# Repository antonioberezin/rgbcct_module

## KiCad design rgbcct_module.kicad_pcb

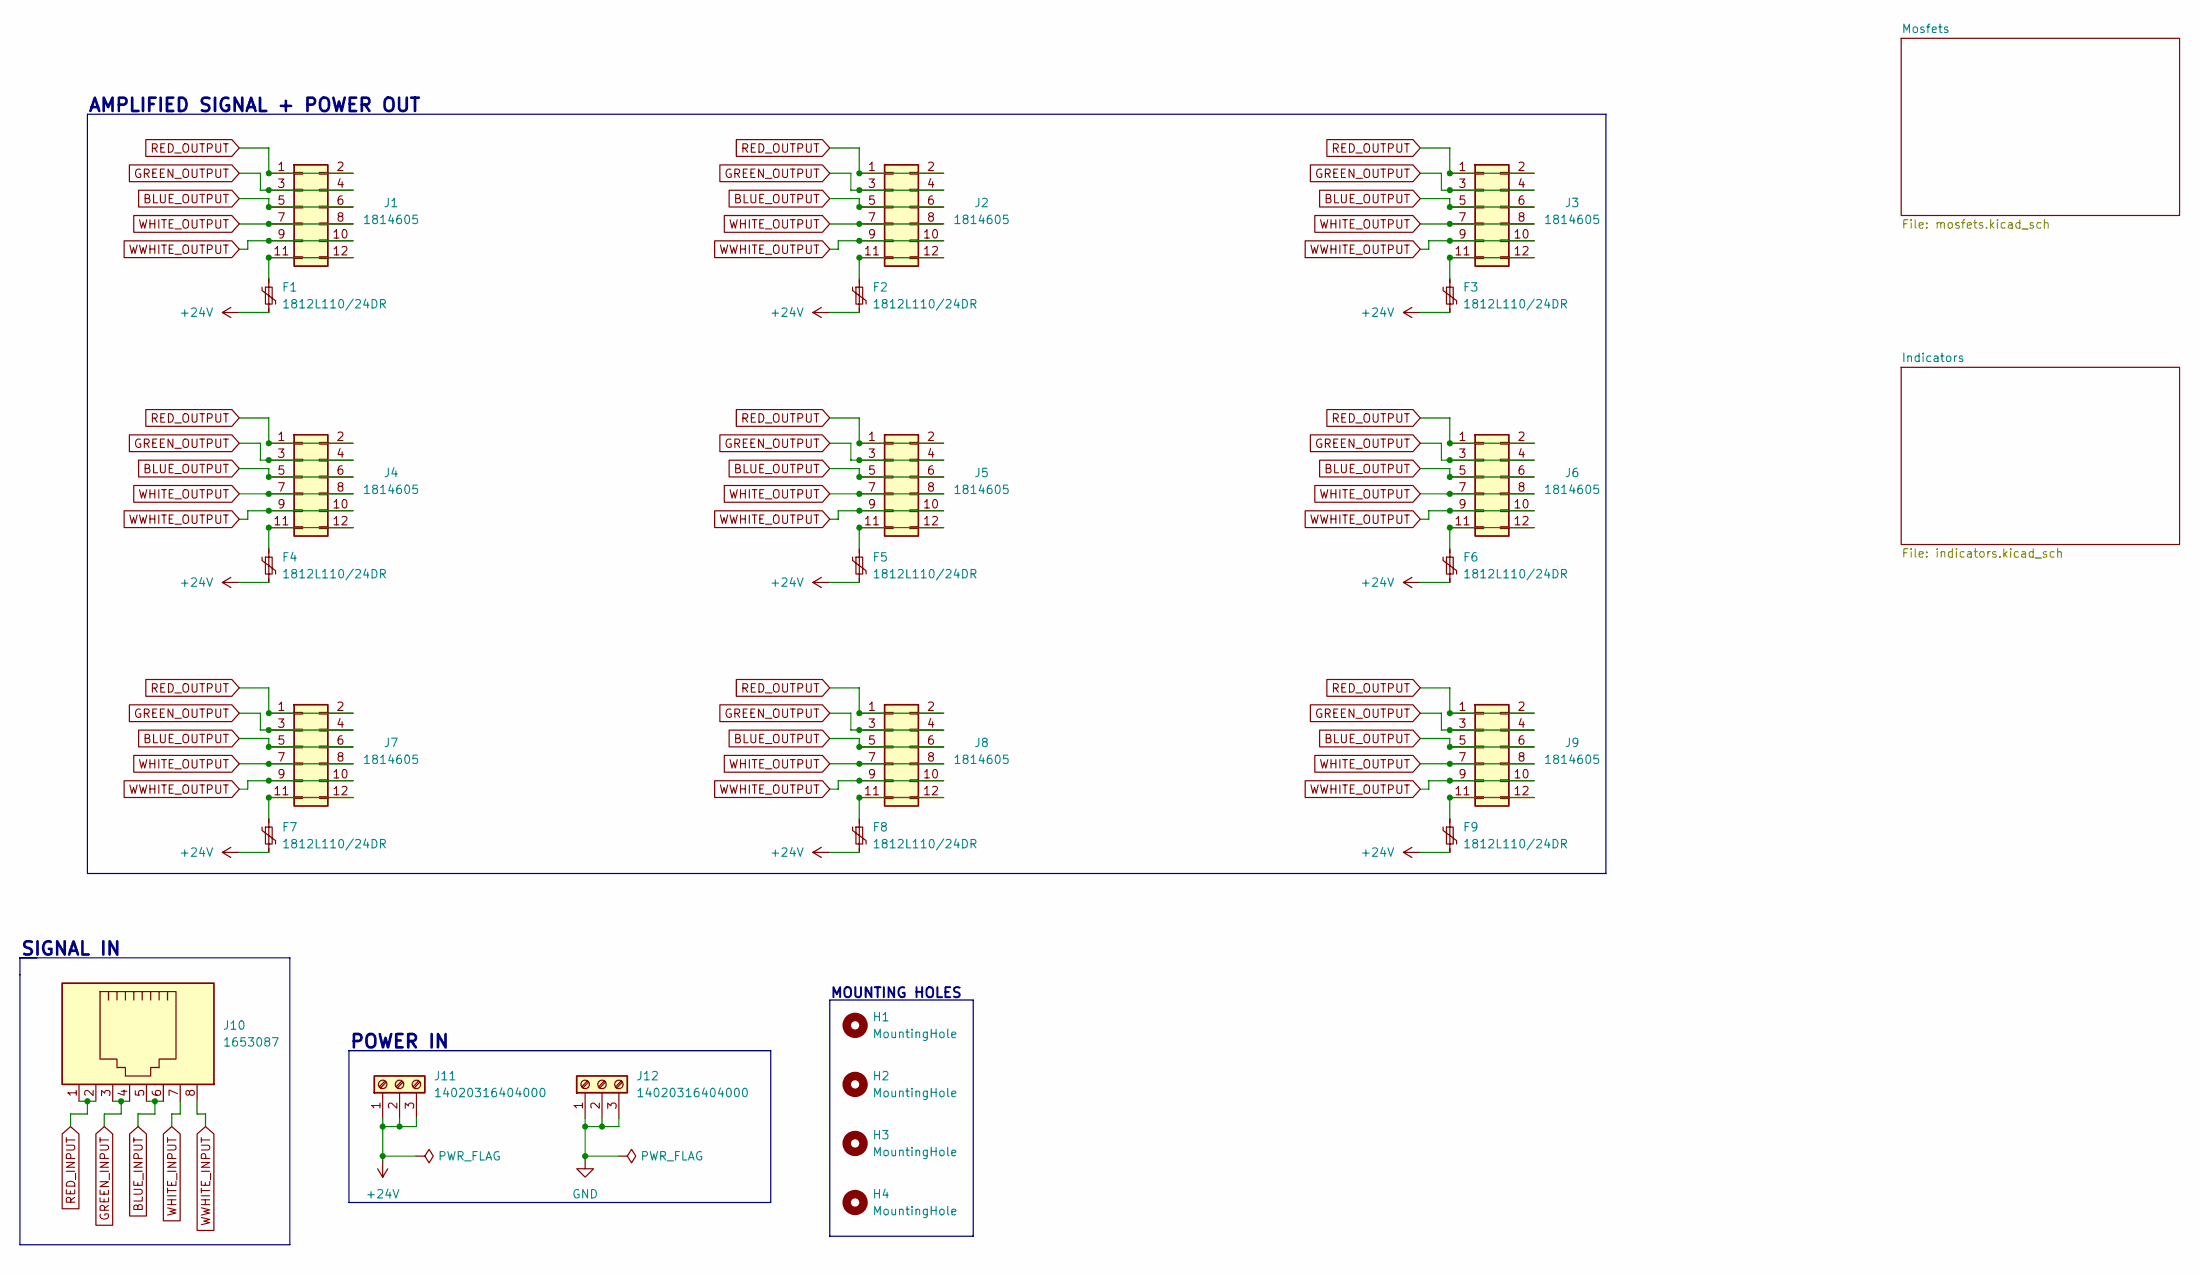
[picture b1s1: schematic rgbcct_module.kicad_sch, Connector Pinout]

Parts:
F1, F2, F3, F4, F5, F6, F7, F8, F9: 1812L110/24DR; 1812L110
H1, H2, H3, H4: MountingHole; MountingHole_3.2mm_M3
J1, J2, J3, J4, J5, J6, J7, J8, J9: 1814605
J10: 1653087
J11, J12: 14020316404000

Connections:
+24V: F1.2, F2.2, F3.2, F4.2, F5.2, F6.2, F7.2, F8.2, F9.2, J11.1, J11.2, J11.3; also elsewhere on the board
BLUE_INPUT: J10.5, J10.6; also elsewhere on the board
BLUE_OUTPUT: J1.5, J1.6, J2.5, J2.6, J3.5, J3.6, J4.5, J4.6, J5.5, J5.6, J6.5, J6.6, J7.5, J7.6, J8.5, J8.6, J9.5, J9.6; also elsewhere on the board
GND: J10.9, J10.10, J10.11, J10.12, J12.1, J12.2, J12.3; also elsewhere on the board
GREEN_INPUT: J10.3, J10.4; also elsewhere on the board
GREEN_OUTPUT: J1.3, J1.4, J2.3, J2.4, J3.3, J3.4, J4.3, J4.4, J5.3, J5.4, J6.3, J6.4, J7.3, J7.4, J8.3, J8.4, J9.3, J9.4; also elsewhere on the board
unnamed: F1.1, J1.11, J1.12
unnamed: F2.1, J2.11, J2.12
unnamed: F3.1, J3.11, J3.12
unnamed: F4.1, J4.11, J4.12
unnamed: F5.1, J5.11, J5.12
unnamed: F6.1, J6.11, J6.12
unnamed: F7.1, J7.11, J7.12
unnamed: F8.1, J8.11, J8.12
unnamed: F9.1, J9.11, J9.12
RED_INPUT: J10.1, J10.2; also elsewhere on the board
RED_OUTPUT: J1.1, J1.2, J2.1, J2.2, J3.1, J3.2, J4.1, J4.2, J5.1, J5.2, J6.1, J6.2, J7.1, J7.2, J8.1, J8.2, J9.1, J9.2; also elsewhere on the board
WHITE_INPUT: J10.7; also elsewhere on the board
WHITE_OUTPUT: J1.7, J1.8, J2.7, J2.8, J3.7, J3.8, J4.7, J4.8, J5.7, J5.8, J6.7, J6.8, J7.7, J7.8, J8.7, J8.8, J9.7, J9.8; also elsewhere on the board
WWHITE_INPUT: J10.8; also elsewhere on the board
WWHITE_OUTPUT: J1.9, J1.10, J2.9, J2.10, J3.9, J3.10, J4.9, J4.10, J5.9, J5.10, J6.9, J6.10, J7.9, J7.10, J8.9, J8.10, J9.9, J9.10; also elsewhere on the board

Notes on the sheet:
MOUNTING HOLES
SIGNAL IN
AMPLIFIED SIGNAL + POWER OUT
POWER IN

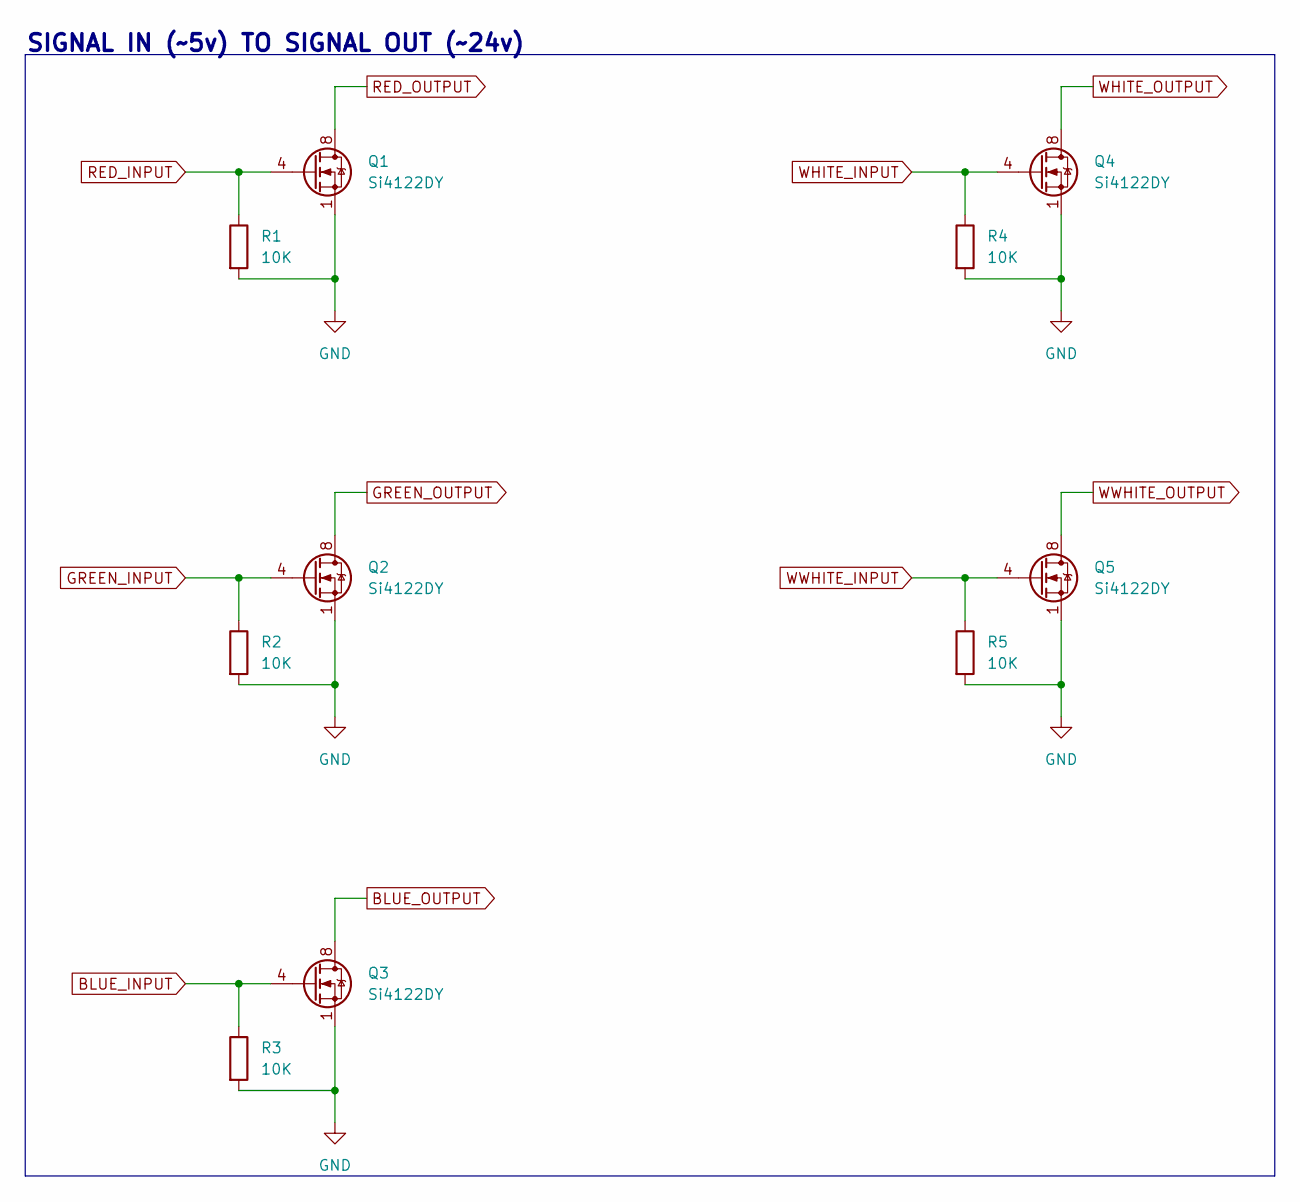
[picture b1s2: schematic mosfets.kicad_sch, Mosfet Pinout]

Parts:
Q1, Q2, Q3, Q4, Q5: Si4122DY
R1, R2, R3, R4, R5: 10K; Panasonic_ERJ_0805

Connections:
BLUE_INPUT: Q3.4 (G), R3.1; also elsewhere on the board
BLUE_OUTPUT: Q3.5 (D), Q3.6 (D), Q3.7 (D), Q3.8 (D); also elsewhere on the board
GND: Q1.1 (S), Q1.2 (S), Q1.3 (S), Q2.1 (S), Q2.2 (S), Q2.3 (S), Q3.1 (S), Q3.2 (S), Q3.3 (S), Q4.1 (S), Q4.2 (S), Q4.3 (S), Q5.1 (S), Q5.2 (S), Q5.3 (S), R1.2, R2.2, R3.2, R4.2, R5.2; also elsewhere on the board
GREEN_INPUT: Q2.4 (G), R2.1; also elsewhere on the board
GREEN_OUTPUT: Q2.5 (D), Q2.6 (D), Q2.7 (D), Q2.8 (D); also elsewhere on the board
RED_INPUT: Q1.4 (G), R1.1; also elsewhere on the board
RED_OUTPUT: Q1.5 (D), Q1.6 (D), Q1.7 (D), Q1.8 (D); also elsewhere on the board
WHITE_INPUT: Q4.4 (G), R4.1; also elsewhere on the board
WHITE_OUTPUT: Q4.5 (D), Q4.6 (D), Q4.7 (D), Q4.8 (D); also elsewhere on the board
WWHITE_INPUT: Q5.4 (G), R5.1; also elsewhere on the board
WWHITE_OUTPUT: Q5.5 (D), Q5.6 (D), Q5.7 (D), Q5.8 (D); also elsewhere on the board

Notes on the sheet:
SIGNAL IN (~5v) TO SIGNAL OUT (~24v)

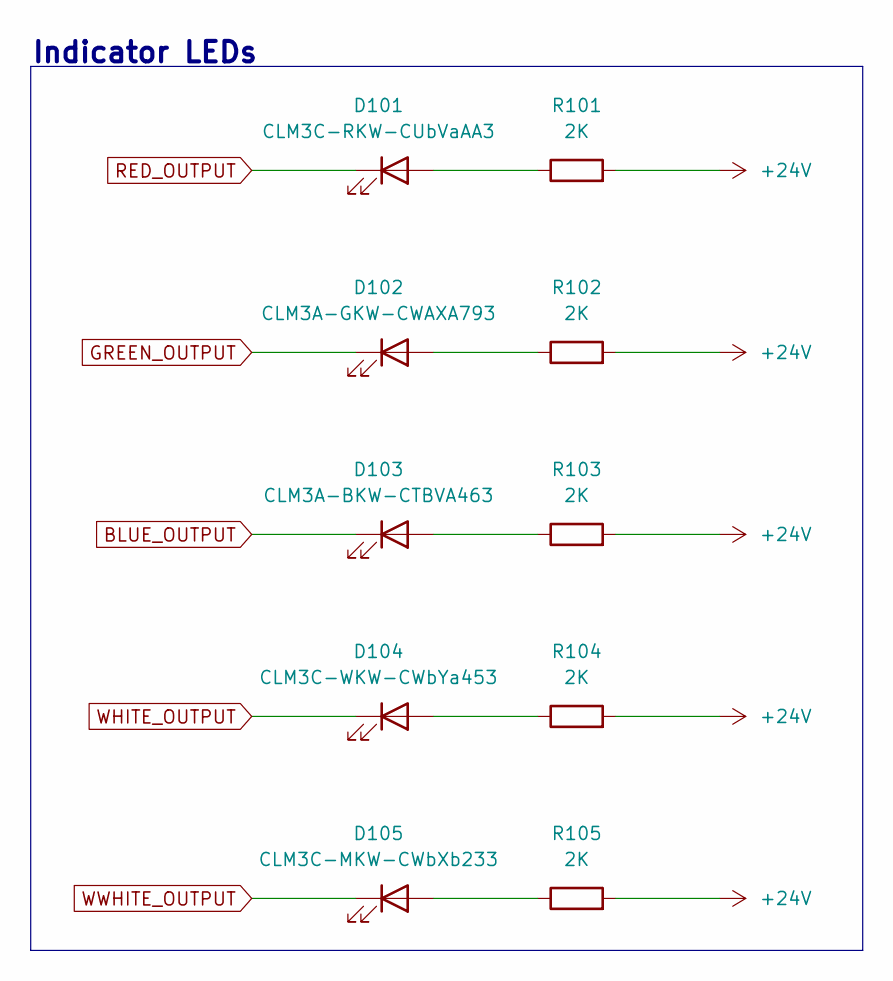
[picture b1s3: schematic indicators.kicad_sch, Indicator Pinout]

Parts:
D101: CLM3C-RKW-CUbVaAA3; Cree LED CLM3C
D102: CLM3A-GKW-CWAXA793; Cree LED CLM3C
D103: CLM3A-BKW-CTBVA463; Cree LED CLM3C
D104: CLM3C-WKW-CWbYa453; Cree LED CLM3C
D105: CLM3C-MKW-CWbXb233; Cree LED CLM3C
R101, R102, R103, R104, R105: 2K; Panasonic_ERJ_0805

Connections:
+24V: R101.2, R102.2, R103.2, R104.2, R105.2; also elsewhere on the board
BLUE_OUTPUT: D103.1 (K); also elsewhere on the board
GREEN_OUTPUT: D102.1 (K); also elsewhere on the board
unnamed: D101.2 (A), R101.1
unnamed: D102.2 (A), R102.1
unnamed: D103.2 (A), R103.1
unnamed: D104.2 (A), R104.1
unnamed: D105.2 (A), R105.1
RED_OUTPUT: D101.1 (K); also elsewhere on the board
WHITE_OUTPUT: D104.1 (K); also elsewhere on the board
WWHITE_OUTPUT: D105.1 (K); also elsewhere on the board

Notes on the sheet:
Indicator LEDs

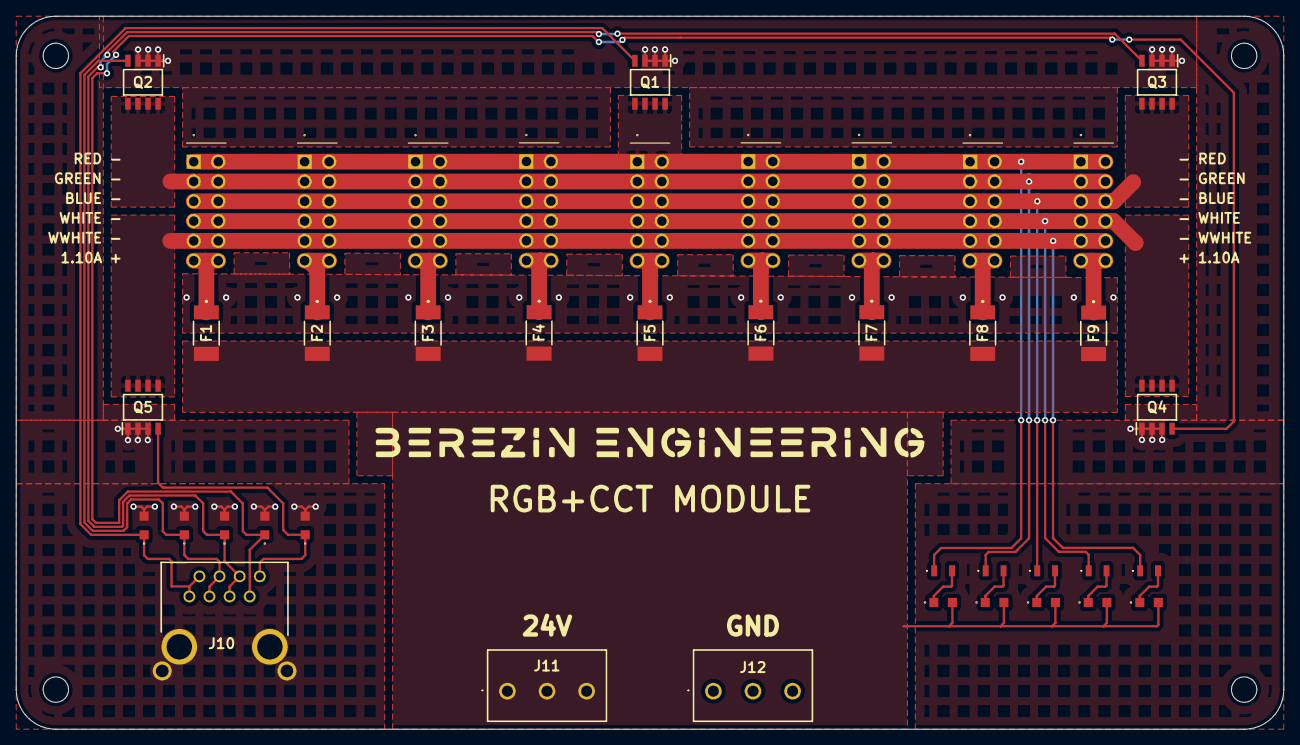
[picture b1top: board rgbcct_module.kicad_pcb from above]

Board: 2 copper layers, 160.0 x 90.0 mm, 45 parts (0 on the bottom side), 26 nets.
